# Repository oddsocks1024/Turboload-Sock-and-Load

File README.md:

# TurboLoad Sock & Load Edition

## Description
A clone of the Australian designed C64 HES/HPD Turboload Cartridge for C64 Disk Drives

**Features**
* Speeds up the load of floppy disks by up to 6 times
* Adds additional DOS commands
* Create and load disk menus
* Reset Button
* Power LED
* Compatible with the JACC64-16K case

## Bill of Materials

| Qty | Component                    |
|:---:|------------------------------|
| 1   | 470nF Tantalum Capacitor     |
| 2   | 100nF Ceramic Capacitors     |
| 1   | 5mm LED                      |
| 1   | 330Ω Axial Resistor (LED)    |
| 1   | 4.7KΩ Axial Resistor         |
| 1   | 10KΩ Axial Resistor          |
| 1   | 6mm Tactile Switch           |
| 1   | 74LS09 14pin DIP             |
| 1   | 27C64 or compatible (E)EPROM |

* IC sockets optional.
* The LED resistor is nominally 330Ω but anything up to 1K usually is fine
* Larger EPROMS/EEPROMS can generally be used but repeat the image to fill up the ROM

## DOS Commands
Typing @H and RETURN will bring up a help screen which lists the commands.

### @
Toggle TURBOLOAD on and off. The screen colours will be C64 standard when TURBOLOAD is off, but will change when TURBOLOAD is on. Other features remain available when TURBOLOAD is off.

### @$
Display the disk directory. This will remove current programs in memory. The listing may be paused by pressing any key. Pressing any key again will resume listing. Pressing the RUN/STOP key will return the READY prompt.

### @B
List a BASIC program in memory to a Commodore compatible printer (device number 4).

### @E
Reads the error channel to display the error type and stop the disk drive error light flashing.

### @D"Filename"
Deletes the file. Files may be deleted using the directory listing by typing @D on the left of the screen, making sure that there are only blank spaces between the @D and the quote mark at the left of the program name.

### @F"Diskname,ID"
Complete format (for new disks).

### @F"Diskname"
Short format, clears the disk directory (existing programs may be recoverable – refer to disk drive manual).

### @L"Filename"
Loads a program, equivalent to LOAD"Filename",8,1. Files can be loaded using the directory listing by typing @L on the left of the screen, making sure that there are only blank spaces between the @L and the quote mark at the left of the program name.

### @L
Loads the first file on the disk.

### @M
Displays the TURBOMENU screen (refer next section).

### @P
Dumps screen text to a Commodore compatible printer (device number 4). This can also be called from within a program by using SYS57046.

### @V
Validates a disk.

### @"Command"
Sends a command to the disk drive (e.g. @"R0:new name=old name" to rename a file).

## 3D Printable Case
This PCB is designed to be compatible with the case for the JACC64-16K cartridge. Please see that repository for details.

## Support Me
Everything is freely available so you can make your own PCB and case, however if you would like to support me, please see the following links.

* [My Projects](https://projects.amiga-hardware.com) - Donate on this page
* [Order the TurboLoad Sock & Load PCB](https://www.pcbway.com/project/shareproject/C64_Turboload_Sock_Load_Edition_820318a7.html)
* [Order the JACC64-16K Case which is compatible](https://www.pcbway.com/project/shareproject/JACC64_16K_C64_Cartridge_Case_78ec0fd1.html)

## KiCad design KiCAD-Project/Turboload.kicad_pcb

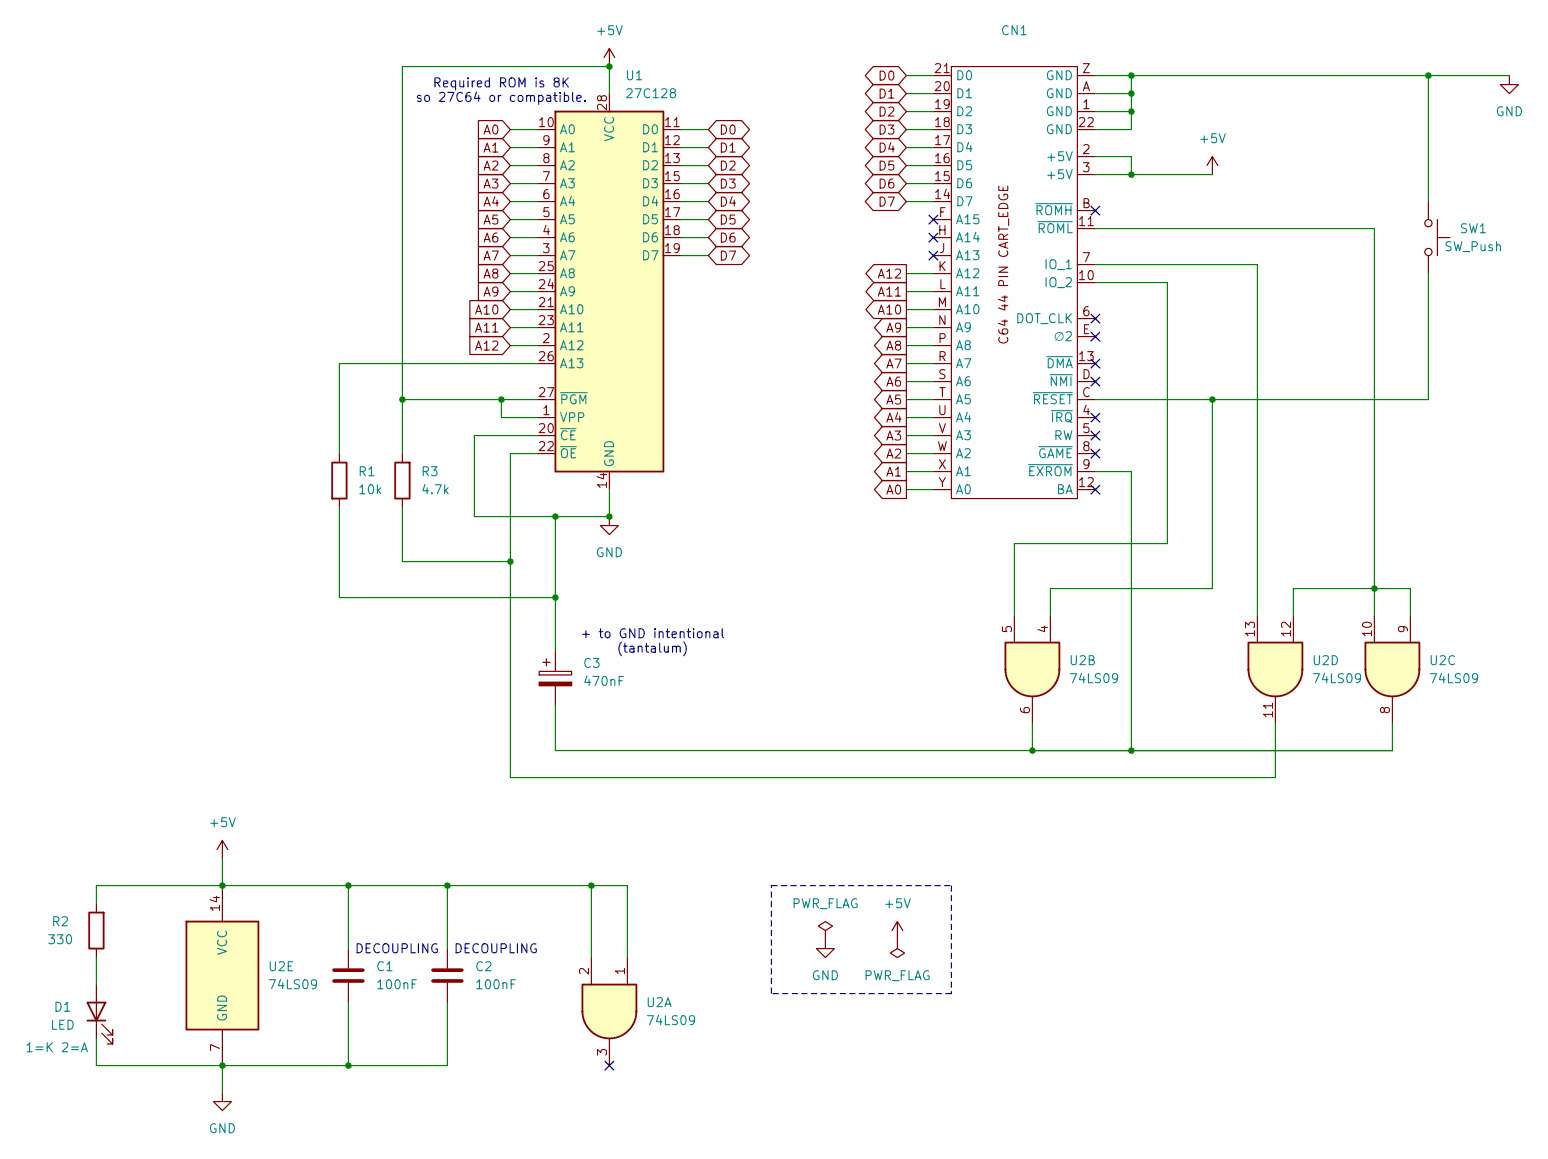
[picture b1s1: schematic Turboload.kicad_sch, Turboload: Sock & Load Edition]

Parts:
C1, C2: 100nF; C_Disc_D3.0mm_W2.0mm_P2.50mm
C3: 470nF; C_Disc_D3.0mm_W2.0mm_P2.50mm
CN1: C64 Expansion
D1: LED; LED_D5.0mm
R1: 10k; R_Axial_DIN0207_L6.3mm_D2.5mm_P10.16mm_Horizontal
R2: 330; R_Axial_DIN0207_L6.3mm_D2.5mm_P10.16mm_Horizontal
R3: 4.7k; R_Axial_DIN0207_L6.3mm_D2.5mm_P10.16mm_Horizontal
SW1: SW_Push; SW_PUSH_6mm
U1: 27C128; DIP-28_W15.24mm
U2: 74LS09; DIP-14_W7.62mm

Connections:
+5V: C1.2, C2.2, CN1.2 (+5V), CN1.3 (+5V), R2.2, R3.2, U1.1 (VPP), U1.27 (~PGM), U1.28 (VCC), U2.1, U2.2, U2.14 (VCC)
A0: CN1.Y (A0), U1.10 (A0)
A1: CN1.X (A1), U1.9 (A1)
A2: CN1.W (A2), U1.8 (A2)
A3: CN1.V (A3), U1.7 (A3)
A4: CN1.U (A4), U1.6 (A4)
A5: CN1.T (A5), U1.5 (A5)
A6: CN1.S (A6), U1.4 (A6)
A7: CN1.R (A7), U1.3 (A7)
A8: CN1.P (A8), U1.25 (A8)
A9: CN1.N (A9), U1.24 (A9)
A10: CN1.M (A10), U1.21 (A10)
A11: CN1.L (A11), U1.23 (A11)
A12: CN1.K (A12), U1.2 (A12)
D0: CN1.21 (D0), U1.11 (D0)
D1: CN1.20 (D1), U1.12 (D1)
D2: CN1.19 (D2), U1.13 (D2)
D3: CN1.18 (D3), U1.15 (D3)
D4: CN1.17 (D4), U1.16 (D4)
D5: CN1.16 (D5), U1.17 (D5)
D6: CN1.15 (D6), U1.18 (D6)
D7: CN1.14 (D7), U1.19 (D7)
GND: C1.1, C2.1, C3.1, CN1.1 (GND), CN1.22 (GND), CN1.A (GND), CN1.Z (GND), D1.1 (K), R1.2, SW1.1, U1.14 (GND), U1.20 (~CE), U2.7 (GND)
unnamed: CN1.7 (IO_1), U2.13
unnamed: CN1.10 (IO_2), U2.5
unnamed: C3.2, CN1.9 (~EXROM), U2.6, U2.8
unnamed: CN1.C (~RESET), SW1.2, U2.4
unnamed: CN1.11 (~ROML), U2.9, U2.10, U2.12
unnamed: D1.2 (A), R2.1
unnamed: R1.1, U1.26 (A13)
unnamed: R3.1, U1.22 (~OE), U2.11

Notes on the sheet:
DECOUPLING
+ to GND intentional (tantalum)
Required ROM is 8K so 27C64 or compatible.

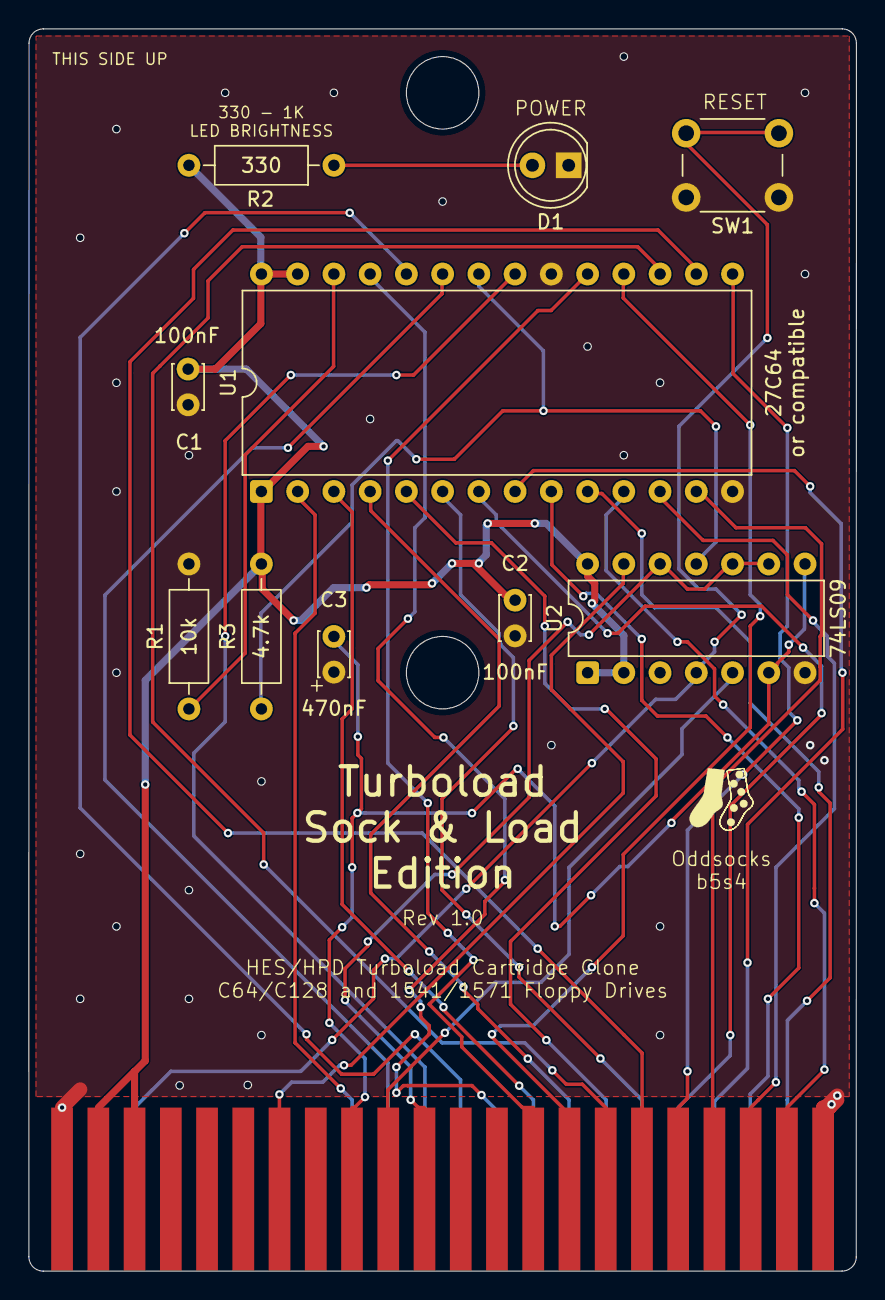
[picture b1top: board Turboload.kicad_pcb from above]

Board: 2 copper layers, 58.0 x 87.1 mm, 11 parts (0 on the bottom side), 31 nets.
